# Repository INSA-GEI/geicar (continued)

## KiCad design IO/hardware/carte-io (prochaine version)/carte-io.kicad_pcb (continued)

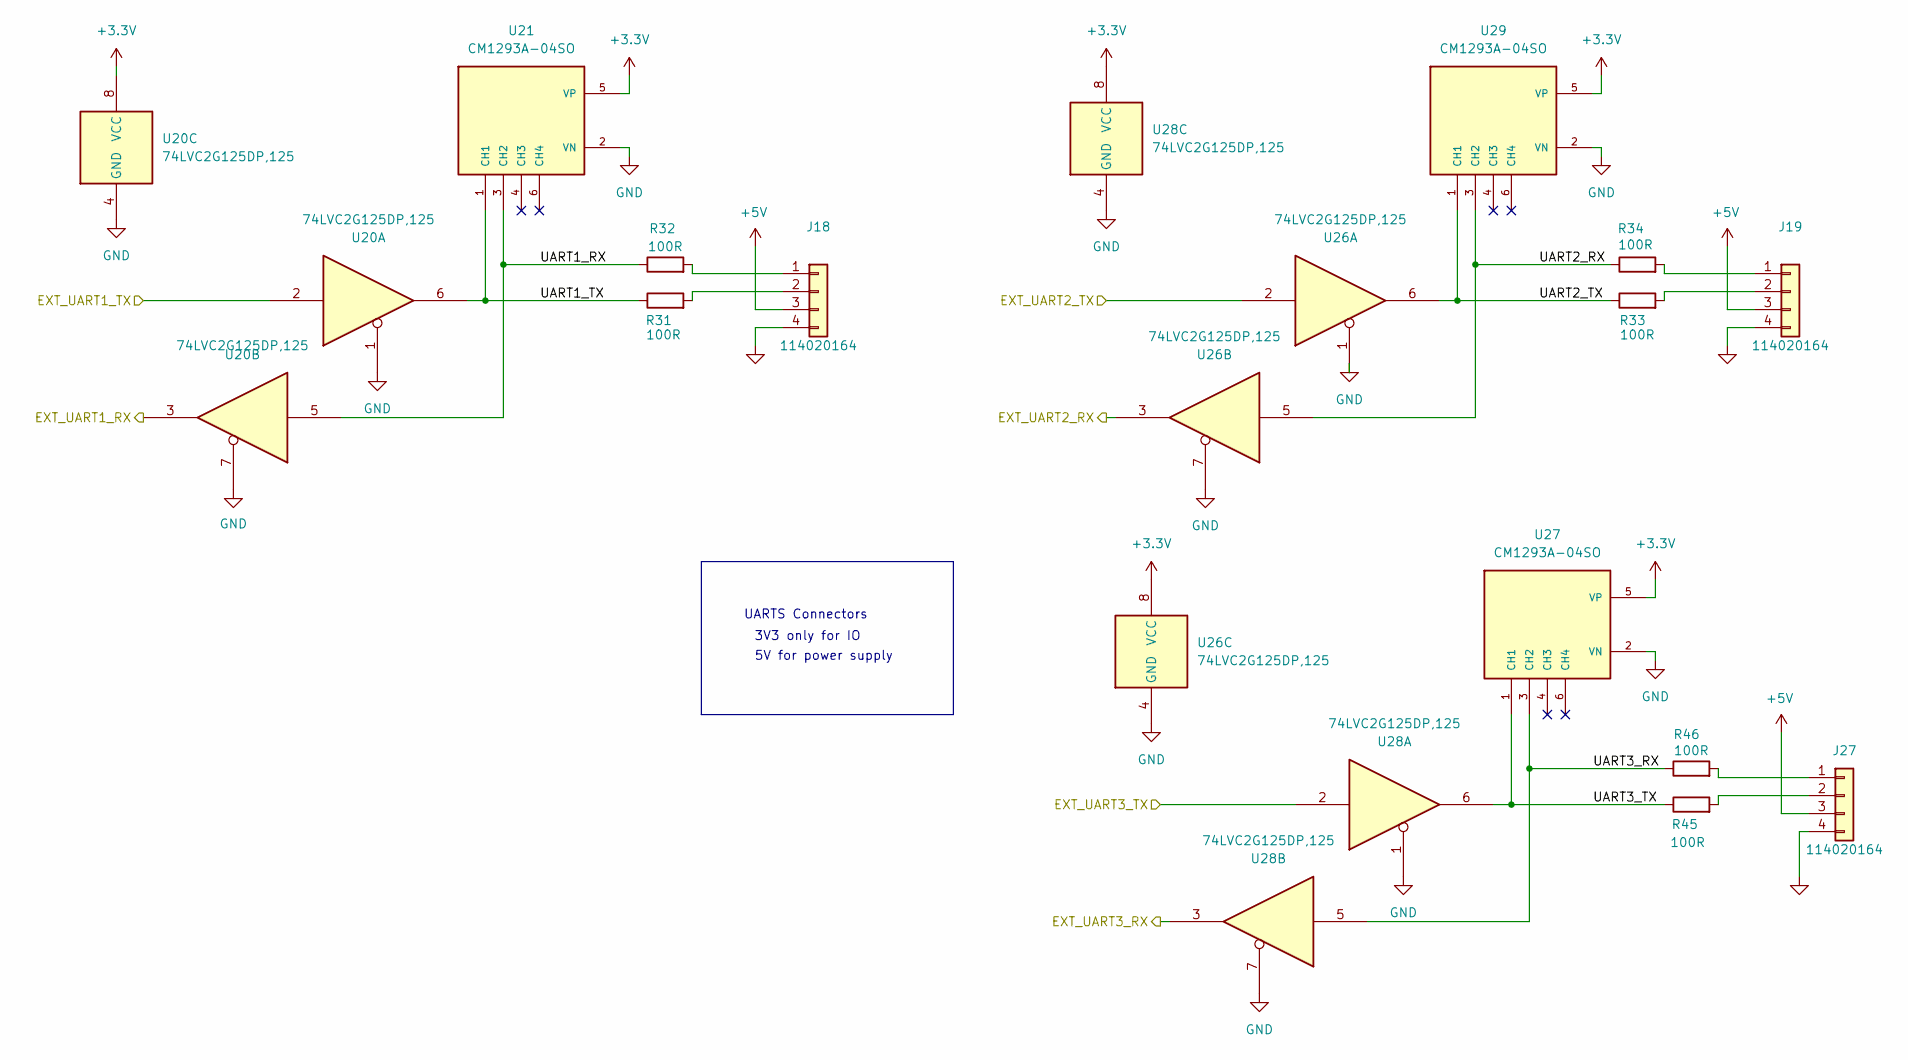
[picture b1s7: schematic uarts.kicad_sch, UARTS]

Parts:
J18, J19, J27: 114020164; SEEEDSTUDIO_114020164
R31, R32, R33, R34, R45, R46: 100R; R_0805_2012Metric_Pad1.20x1.40mm_HandSolder
U20, U26, U28: 74LVC2G125DP,125; TSSOP-8_3x3mm_P0.65mm
U21, U27, U29: CM1293A-04SO; SOT95P285X140-6N

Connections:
+3.3V: U20.8 (VCC), U21.5 (VP), U26.8 (VCC), U27.5 (VP), U28.8 (VCC), U29.5 (VP); also elsewhere on the board
+5V: J18.3, J19.3, J27.3; also elsewhere on the board
/CPU/COM_GPS_RX: U28.2; also elsewhere on the board
/CPU/COM_GPS_TX: U28.3; also elsewhere on the board
/CPU/COM_LIDAR1_RX: U20.3; also elsewhere on the board
/CPU/COM_LIDAR1_TX: U20.2; also elsewhere on the board
/CPU/COM_LIDAR2_RX: U26.3; also elsewhere on the board
/CPU/COM_LIDAR2_TX: U26.2; also elsewhere on the board
/UARTS/UART1_RX: R32.1, U20.5, U21.3 (CH2)
/UARTS/UART1_TX: R31.1, U20.6, U21.1 (CH1)
/UARTS/UART2_RX: R34.1, U26.5, U29.3 (CH2)
/UARTS/UART2_TX: R33.1, U26.6, U29.1 (CH1)
/UARTS/UART3_RX: R46.1, U27.3 (CH2), U28.5
/UARTS/UART3_TX: R45.1, U27.1 (CH1), U28.6
GND: J18.4, J19.4, J27.4, U20.1, U20.4 (GND), U20.7, U21.2 (VN), U26.1, U26.4 (GND), U26.7, U27.2 (VN), U28.1, U28.4 (GND), U28.7, U29.2 (VN); also elsewhere on the board
unnamed: J18.1, R32.2
unnamed: J18.2, R31.2
unnamed: J19.1, R34.2
unnamed: J19.2, R33.2
unnamed: J27.1, R46.2
unnamed: J27.2, R45.2

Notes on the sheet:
UARTS Connectors
5V for power supply
3V3 only for IO

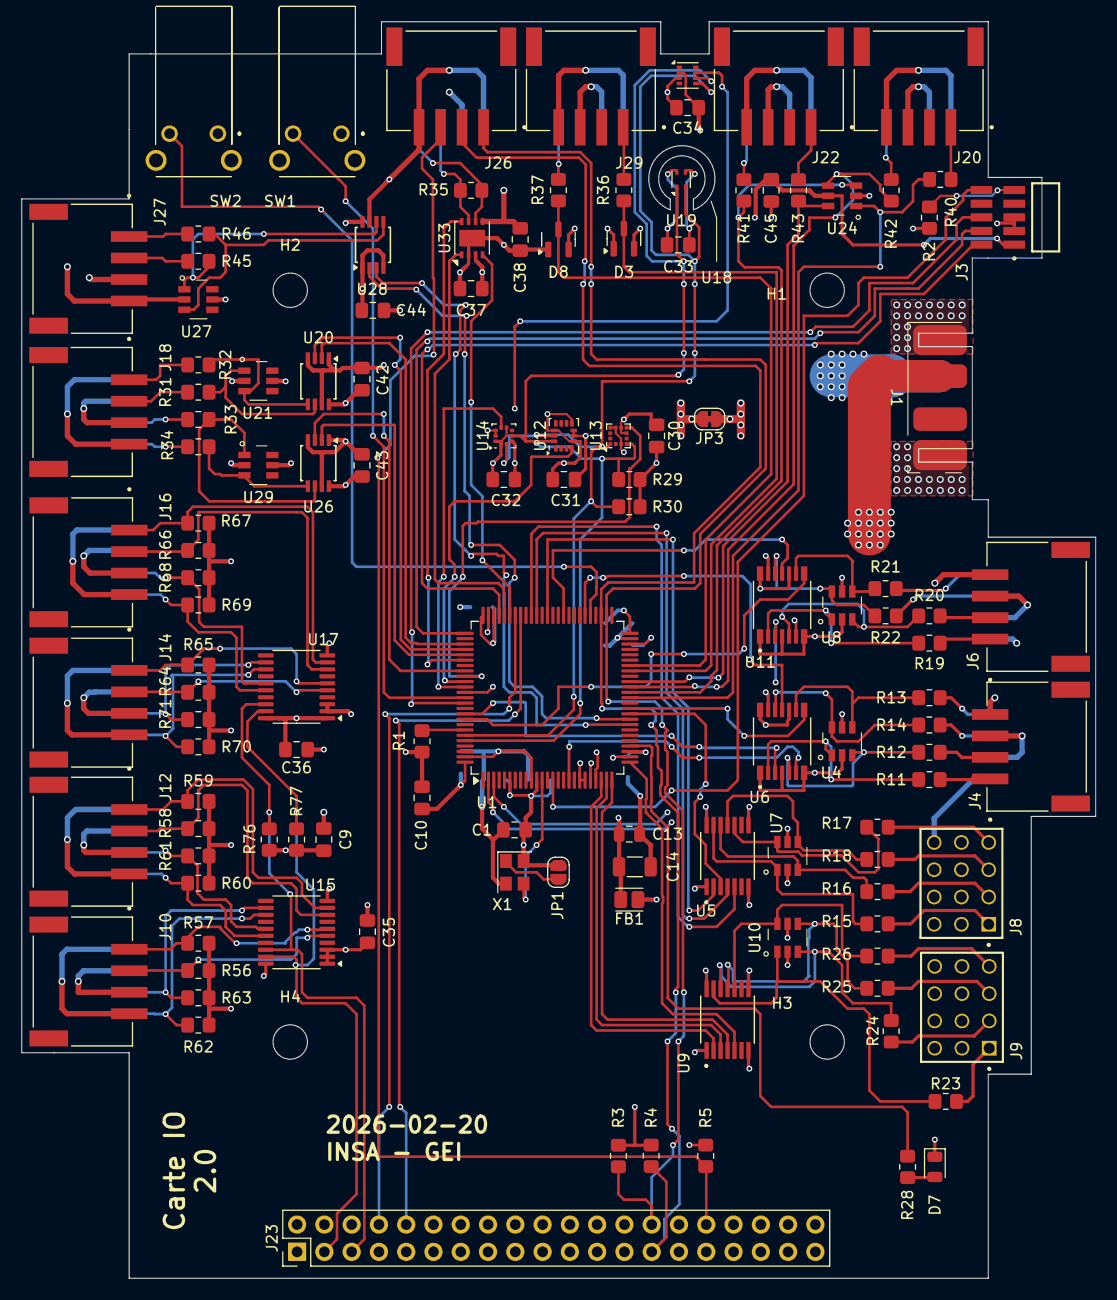
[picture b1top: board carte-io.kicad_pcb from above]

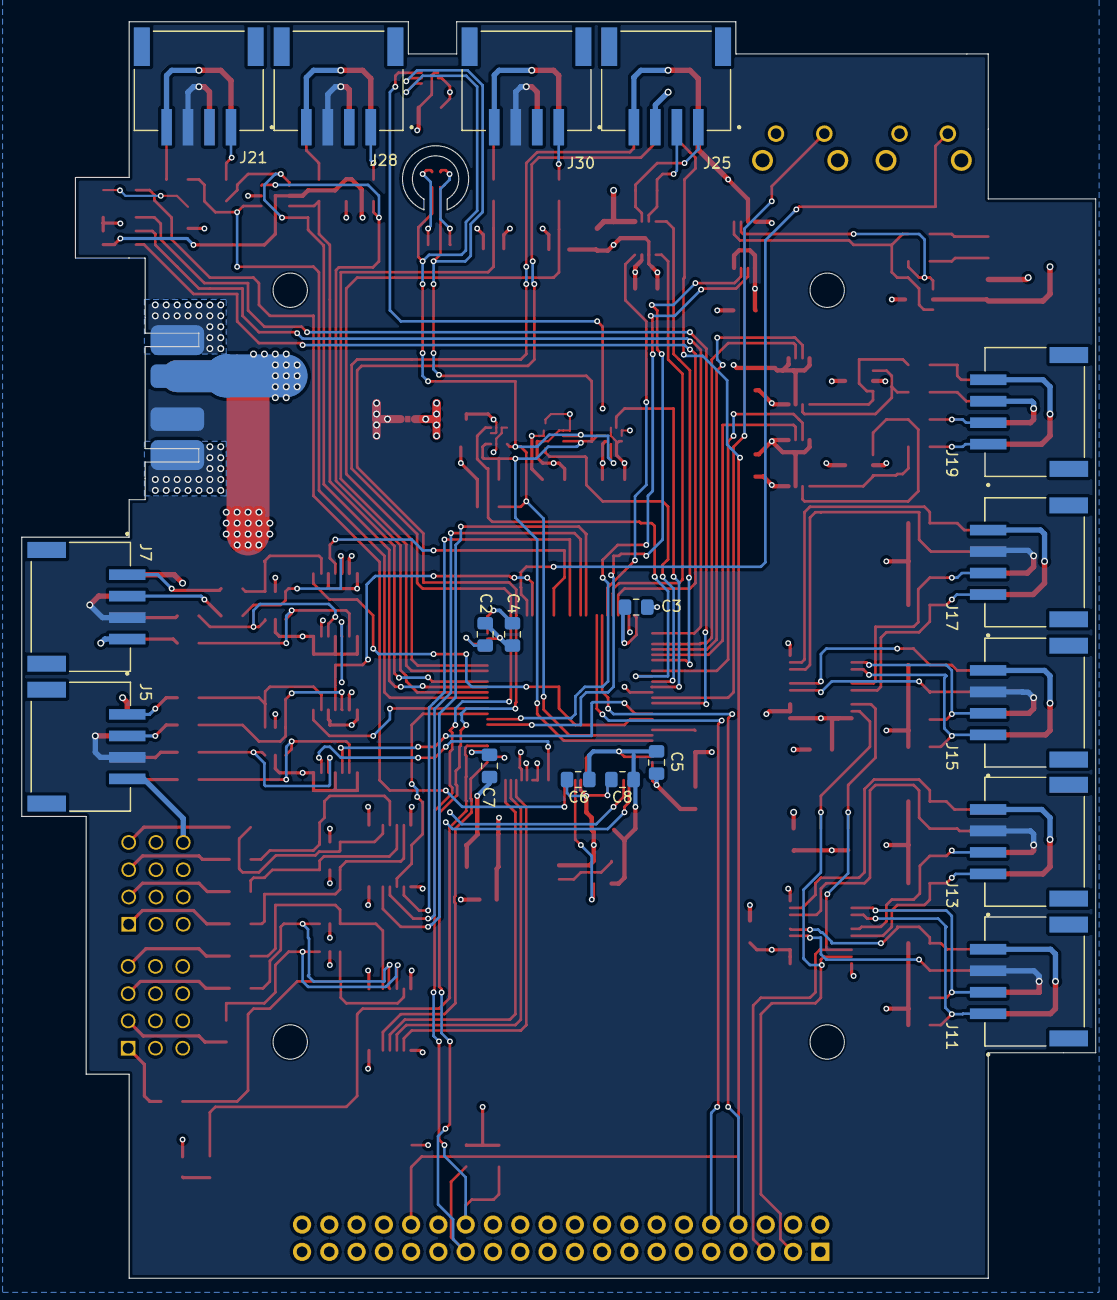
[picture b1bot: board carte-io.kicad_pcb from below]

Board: 4 copper layers, 100.0 x 117.0 mm, 145 parts (18 on the bottom side), 131 nets.

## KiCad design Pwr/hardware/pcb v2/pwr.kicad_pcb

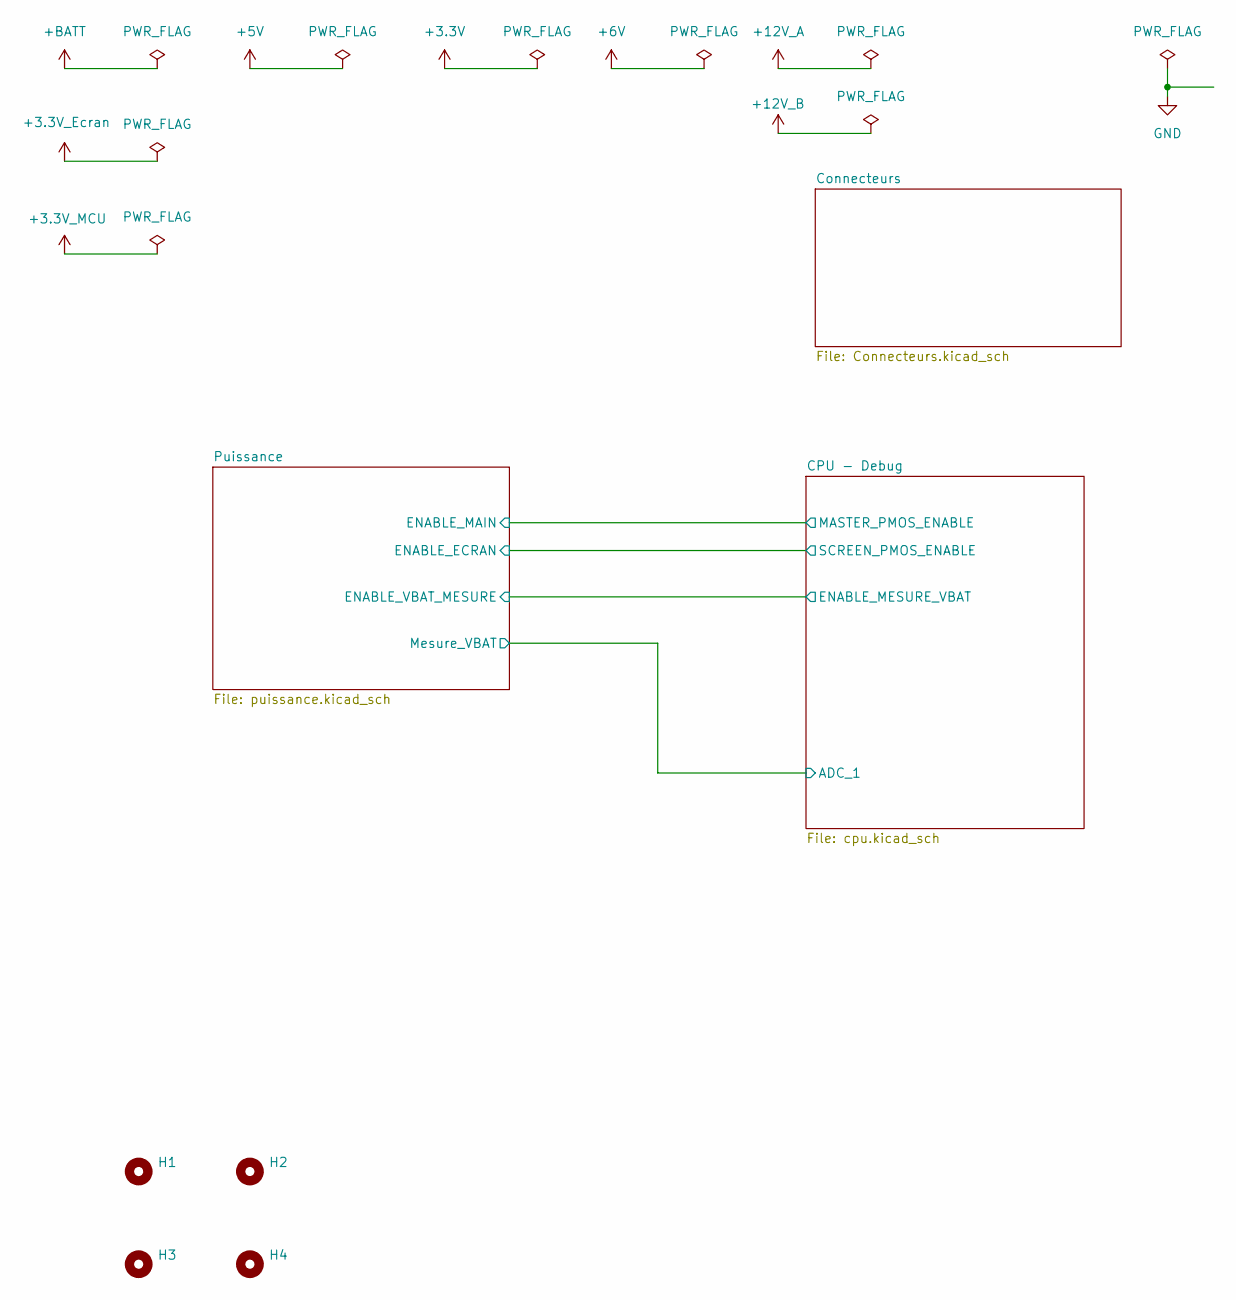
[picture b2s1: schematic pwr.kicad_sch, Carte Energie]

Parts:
H1, H2, H3, H4: MountingHole; MountingHole_3.2mm_M3

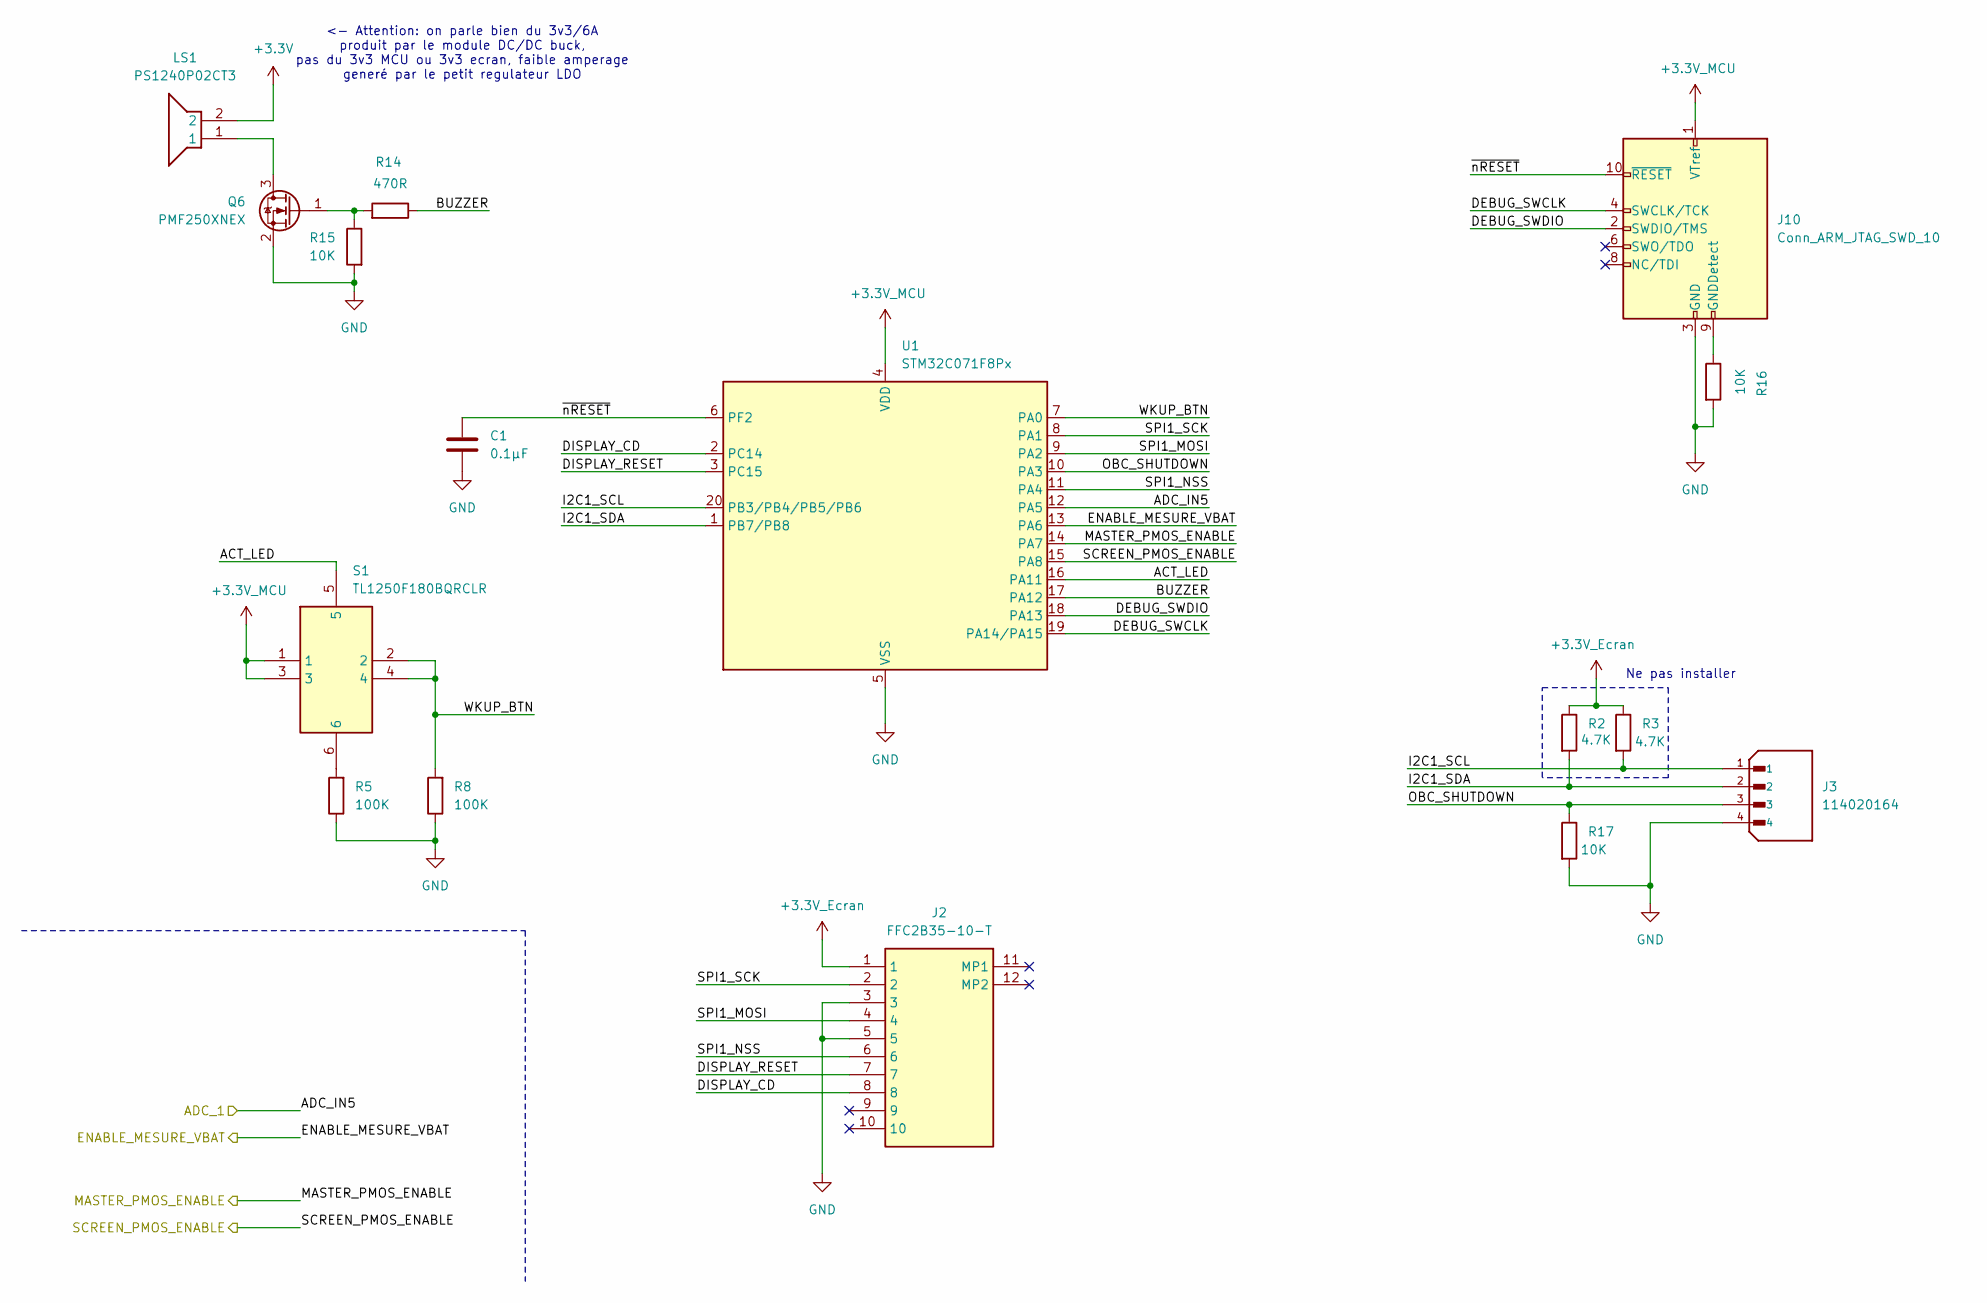
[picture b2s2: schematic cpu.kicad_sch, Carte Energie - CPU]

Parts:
C1: 0.1µF; C_0805_2012Metric
J2: FFC2B35-10-T; FFC2B3510T; Mouser Part Number 640-FFC2B35-10-T
J3: 114020164; SEEEDSTUDIO_114020164; PARTREV 18/5/20
J10: Conn_ARM_JTAG_SWD_10; FTSH10501LDV007K
LS1: PS1240P02CT3; PS1240P02BT; Mouser Part Number 810-PS1240P02CT3
Q6: PMF250XNEX; SOT-323_SC-70
R2, R3: 4.7K; R_0805_2012Metric
R5, R8: 100K; R_0805_2012Metric
R14: 470R; R_0805_2012Metric
R15, R16, R17: 10K; R_0805_2012Metric
S1: TL1250F180BQRCLR; TL1250; Mouser Part Number 612-TL1250F180BQRCLR
U1: STM32C071F8Px; TSSOP-20_4.4x6.5mm_P0.65mm

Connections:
+3.3V: LS1.2; also elsewhere on the board
+3.3V_Ecran: J2.1, R2.1, R3.1; also elsewhere on the board
+3.3V_MCU: J10.1 (VTref), S1.1, S1.3, U1.4 (VDD); also elsewhere on the board
/CPU - Debug/ACT_LED: S1.5, U1.16 (PA11)
/CPU - Debug/ADC_IN5: U1.12 (PA5); also elsewhere on the board
/CPU - Debug/BUZZER: R14.1, U1.17 (PA12)
/CPU - Debug/DEBUG_SWCLK: J10.4 (SWCLK/TCK), U1.19 (PA14/PA15)
/CPU - Debug/DEBUG_SWDIO: J10.2 (SWDIO/TMS), U1.18 (PA13)
/CPU - Debug/DISPLAY_CD: J2.8, U1.2 (PC14)
/CPU - Debug/DISPLAY_RESET: J2.7, U1.3 (PC15)
/CPU - Debug/ENABLE_MESURE_VBAT: U1.13 (PA6); also elsewhere on the board
/CPU - Debug/I2C1_SCL: J3.1, R3.2, U1.20 (PB3/PB4/PB5/PB6)
/CPU - Debug/I2C1_SDA: J3.2, R2.2, U1.1 (PB7/PB8)
/CPU - Debug/MASTER_PMOS_ENABLE: U1.14 (PA7); also elsewhere on the board
/CPU - Debug/OBC_SHUTDOWN: J3.3, R17.1, U1.10 (PA3)
/CPU - Debug/SCREEN_PMOS_ENABLE: U1.15 (PA8); also elsewhere on the board
/CPU - Debug/SPI1_MOSI: J2.4, U1.9 (PA2)
/CPU - Debug/SPI1_NSS: J2.6, U1.11 (PA4)
/CPU - Debug/SPI1_SCK: J2.2, U1.8 (PA1)
/CPU - Debug/WKUP_BTN: R8.2, S1.2, S1.4, U1.7 (PA0)
/CPU - Debug/~nRESET: C1.1, J10.10 (~RESET), U1.6 (PF2)
GND: C1.2, J2.3, J2.5, J3.4, J10.3 (GND), J10.5 (GND), Q6.2 (S), R5.1, R8.1, R15.2, R16.2, R17.2, U1.5 (VSS); also elsewhere on the board
unnamed: J10.9 (GNDDetect), R16.1
unnamed: LS1.1, Q6.3 (D)
unnamed: Q6.1 (G), R14.2, R15.1
unnamed: R5.2, S1.6

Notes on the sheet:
<- Attention: on parle bien du 3v3/6A produit par le module DC/DC buck, pas du 3v3 MCU ou 3v3 ecran, faible amperage generé par le petit regulateur LDO
Ne pas installer

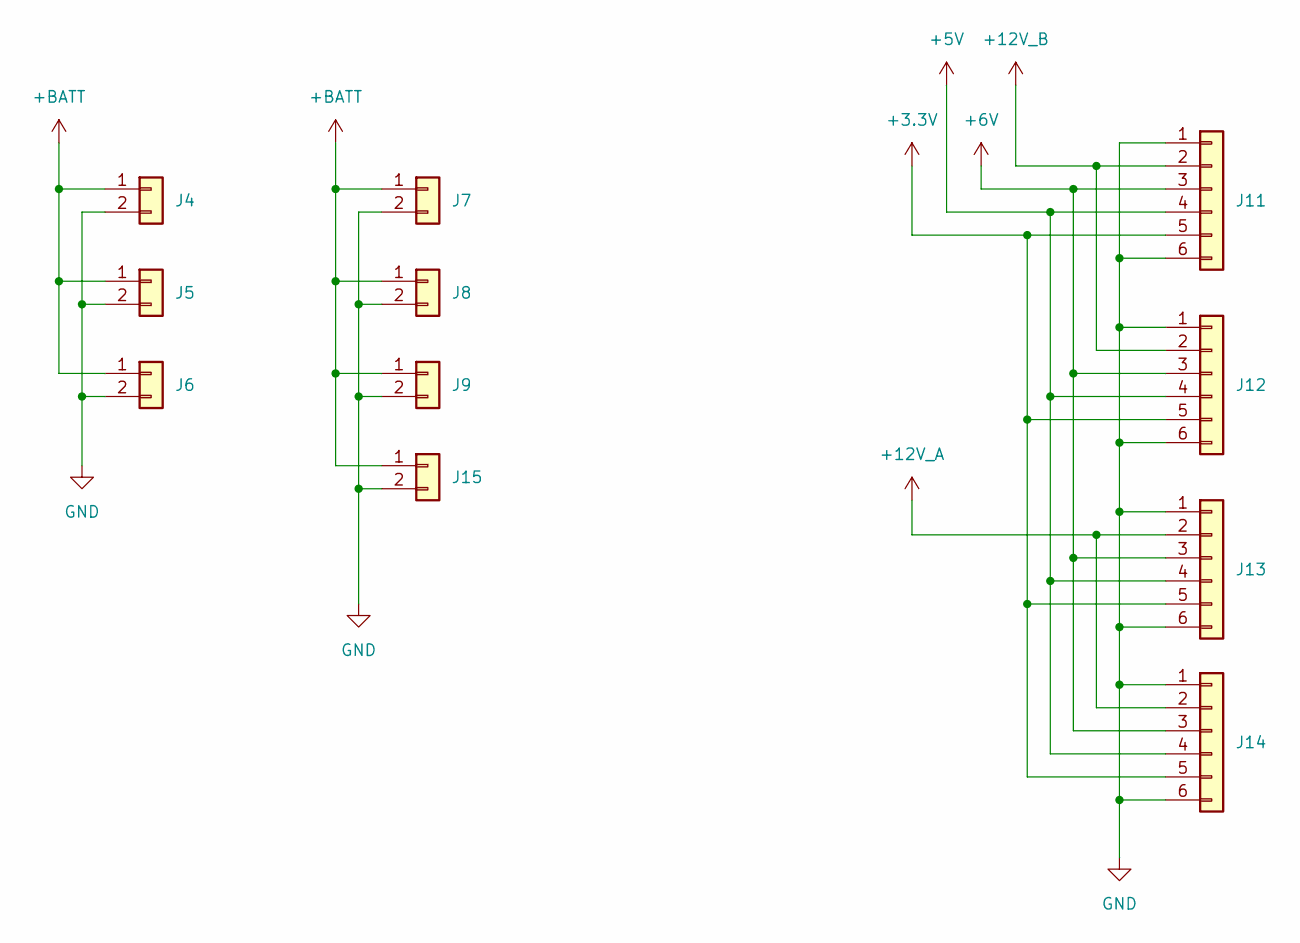
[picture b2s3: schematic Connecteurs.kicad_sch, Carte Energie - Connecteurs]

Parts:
J4, J15: XT60; PAD_XT60
J5, J6, J7, J8, J9: Conn_01x02; PAD_XT60
J11, J12, J13, J14: Conn_01x06; MPX6

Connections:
+3.3V: J11.5, J12.5, J13.5, J14.5; also elsewhere on the board
+5V: J11.4, J12.4, J13.4, J14.4; also elsewhere on the board
+6V: J11.3, J12.3, J13.3, J14.3; also elsewhere on the board
+12V_A: J13.2, J14.2; also elsewhere on the board
+12V_B: J11.2, J12.2; also elsewhere on the board
+BATT: J4.1, J5.1, J6.1, J7.1, J8.1, J9.1, J15.1; also elsewhere on the board
GND: J4.2, J5.2, J6.2, J7.2, J8.2, J9.2, J11.1, J11.6, J12.1, J12.6, J13.1, J13.6, J14.1, J14.6, J15.2; also elsewhere on the board

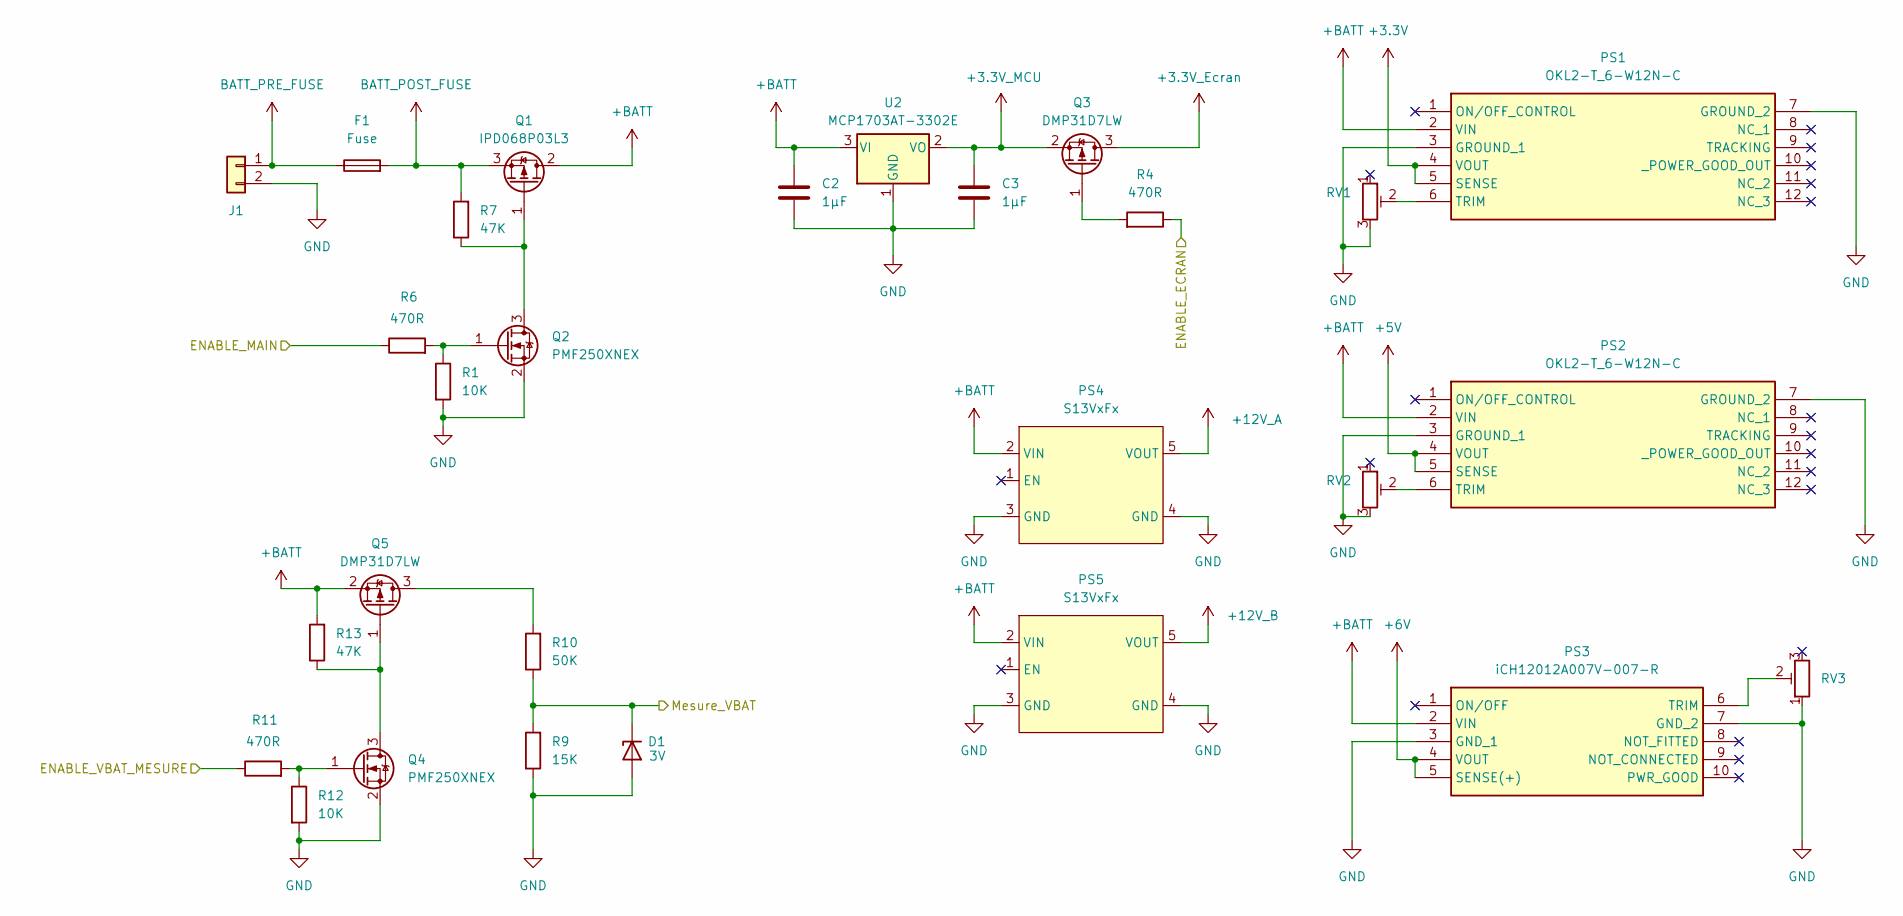
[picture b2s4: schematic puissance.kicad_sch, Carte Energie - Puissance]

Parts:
C2, C3: 1µF; C_0805_2012Metric
D1: 3V; D_SOD-323
F1: Fuse; 3557
J1: XT60; PAD_XT60
PS1, PS2: OKL2-T_6-W12N-C; OKL2T6W12NC; Mouser Part Number 580-OKL2-T/6-W12N-C
PS3: iCH12012A007V-007-R; ICH12012A007V007R; Mouser Part Number 967-ICH12012A007V007
PS4, PS5: S13VxFx
Q1: IPD068P03L3; TO-252-2
Q2, Q4: PMF250XNEX; SOT-323_SC-70
Q3, Q5: DMP31D7LW; SOT-323_SC-70
R1, R12: 10K; R_0805_2012Metric
R4, R6, R11: 470R; R_0805_2012Metric
R7, R13: 47K; R_0805_2012Metric
R9: 15K; R_0805_2012Metric
R10: 50K; R_0805_2012Metric
RV1, RV2, RV3: 3214W-1-202E; Potentiometer_Bourns_3214W_Vertical
U2: MCP1703AT-3302E; SOT-23

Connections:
+3.3V: PS1.4 (VOUT), PS1.5 (SENSE); also elsewhere on the board
+3.3V_Ecran: Q3.3 (D); also elsewhere on the board
+3.3V_MCU: C3.1, Q3.2 (S), U2.2 (VO); also elsewhere on the board
+5V: PS2.4 (VOUT), PS2.5 (SENSE); also elsewhere on the board
+6V: PS3.4 (VOUT), PS3.5 (SENSE(+)); also elsewhere on the board
+12V_A: PS4.5 (VOUT); also elsewhere on the board
+12V_B: PS5.5 (VOUT); also elsewhere on the board
+BATT: C2.1, PS1.2 (VIN), PS2.2 (VIN), PS3.2 (VIN), PS4.2 (VIN), PS5.2 (VIN), Q1.2 (D), Q5.2 (S), R13.2, U2.3 (VI); also elsewhere on the board
/CPU - Debug/ADC_IN5: D1.1 (K), R9.2, R10.1; also elsewhere on the board
/CPU - Debug/ENABLE_MESURE_VBAT: R11.1; also elsewhere on the board
/CPU - Debug/MASTER_PMOS_ENABLE: R6.1; also elsewhere on the board
/CPU - Debug/SCREEN_PMOS_ENABLE: R4.1; also elsewhere on the board
BATT_POST_FUSE: F1.2, Q1.3 (S), R7.2
BATT_PRE_FUSE: F1.1, J1.1
GND: C2.2, C3.2, D1.2 (A), J1.2, PS1.3 (GROUND_1), PS1.7 (GROUND_2), PS2.3 (GROUND_1), PS2.7 (GROUND_2), PS3.3 (GND_1), PS3.7 (GND_2), PS4.3 (GND), PS4.4 (GND), PS5.3 (GND), PS5.4 (GND), Q2.2 (S), Q4.2 (S), R1.2, R9.1, R12.2, RV1.3, RV2.3, RV3.1, U2.1 (GND); also elsewhere on the board
unnamed: PS1.6 (TRIM), RV1.2
unnamed: PS2.6 (TRIM), RV2.2
unnamed: PS3.6 (TRIM), RV3.2
unnamed: Q1.1 (G), Q2.3 (D), R7.1
unnamed: Q2.1 (G), R1.1, R6.2
unnamed: Q3.1 (G), R4.2
unnamed: Q4.3 (D), Q5.1 (G), R13.1
unnamed: Q4.1 (G), R11.2, R12.1
unnamed: Q5.3 (D), R10.2

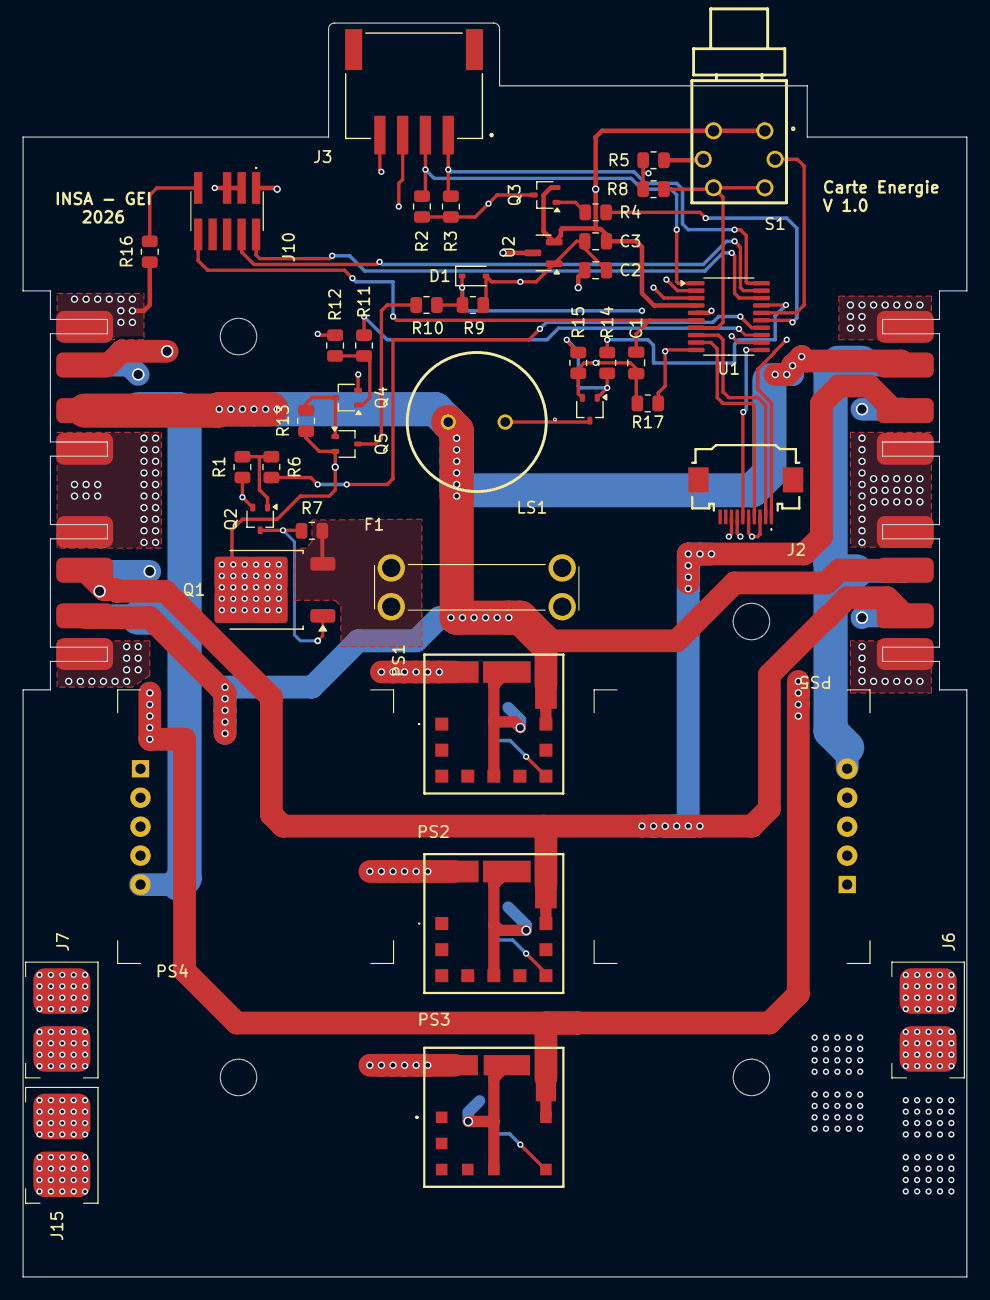
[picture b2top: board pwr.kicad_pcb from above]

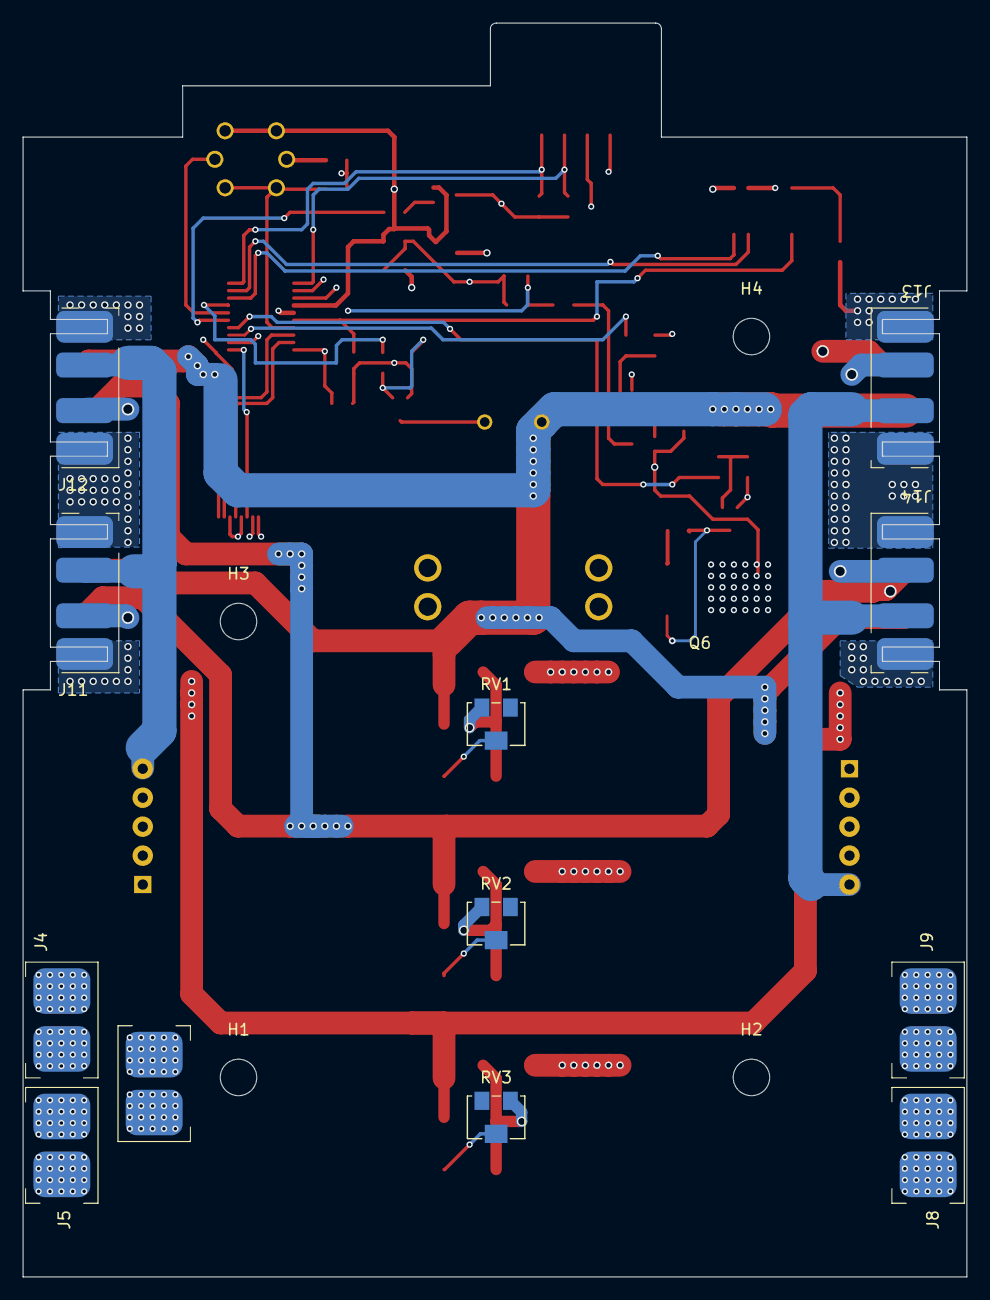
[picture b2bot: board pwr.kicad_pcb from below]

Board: 4 copper layers, 82.8 x 110.0 mm, 59 parts (16 on the bottom side), 42 nets.

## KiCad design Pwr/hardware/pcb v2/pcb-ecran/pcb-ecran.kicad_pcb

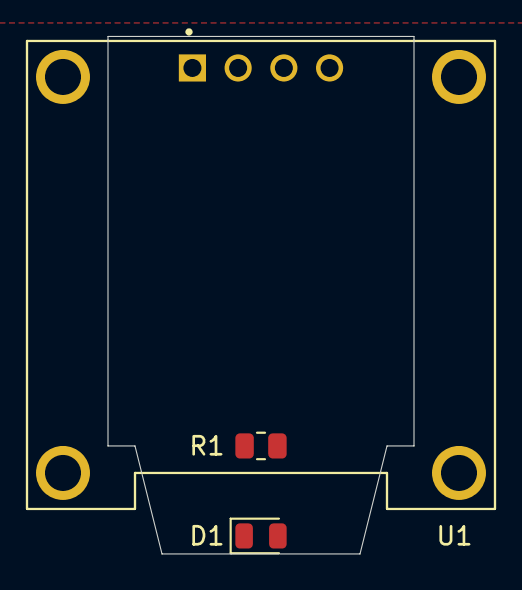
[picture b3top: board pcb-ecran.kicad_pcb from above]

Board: 2 copper layers, 17.0 x 28.8 mm, 4 parts (1 on the bottom side), 6 nets, no tracks yet.

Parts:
D1: APT2012LSECK/J3-PRV; LED_0805_2012Metric
J1: FFC2B35-10-T; FFC2B3510T
R1: 1K; R_0805_2012Metric
U1: DM-OLED096-636; MODULE_DM-OLED096-636

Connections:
+3.3V_Ecran: J1.1, U1.2 (VCC_IN)
/RED_LED: D1.2 (A), J1.7
/SPI_DATA: J1.4, U1.4 (SDA)
/SPI_SCK: J1.2, U1.3 (SCL)
GND: J1.3, J1.5, R1.2, U1.1 (GND)
unnamed: D1.1 (K), R1.1

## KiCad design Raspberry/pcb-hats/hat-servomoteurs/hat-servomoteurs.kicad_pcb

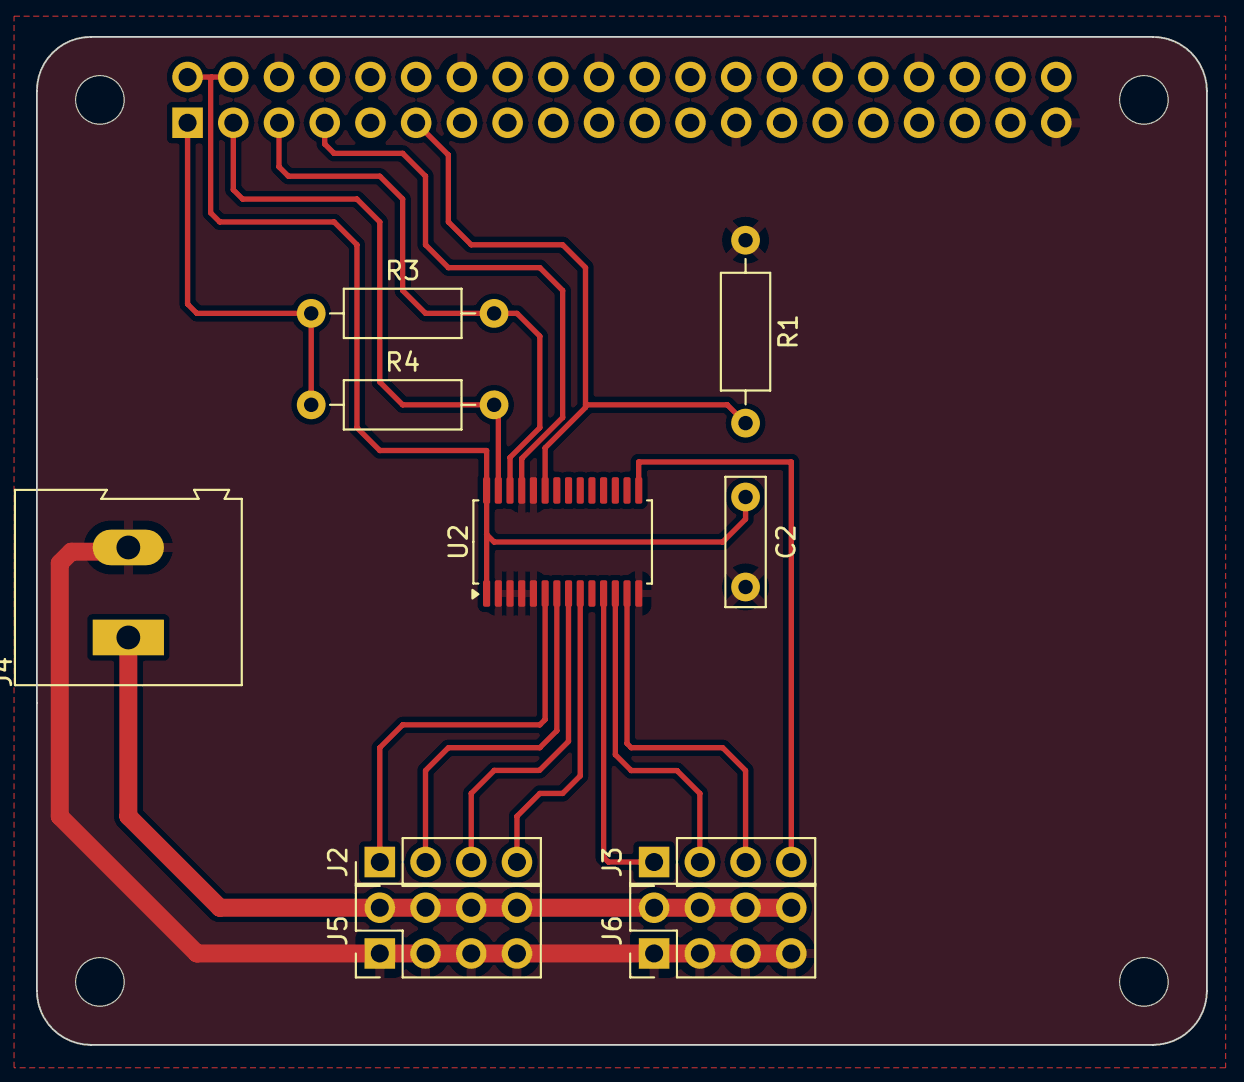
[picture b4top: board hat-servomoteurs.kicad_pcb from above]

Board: 2 copper layers, 65.0 x 56.0 mm, 15 parts (1 on the bottom side), 15 nets.

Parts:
C2: 100nf; C_Rect_L7.0mm_W2.0mm_P5.00mm
J1: GPIO; PinSocket_2x20_P2.54mm_Vertical
J2: Servomoteurs; PinHeader_1x04_P2.54mm_Vertical
J3: ESC; PinHeader_1x04_P2.54mm_Vertical
J4: Conn_01x02; TerminalBlock_Altech_AK300-2_P5.00mm
J5, J6: Conn_02x04_Odd_Even; PinHeader_2x04_P2.54mm_Vertical
MH1, MH2, MH3, MH4: MountingHole_2.7mm_M2.5
R1: 1M; R_Axial_DIN0207_L6.3mm_D2.5mm_P10.16mm_Horizontal
R3, R4: 4.7K; R_Axial_DIN0207_L6.3mm_D2.5mm_P10.16mm_Horizontal
U2: PCA9685PW; TSSOP-28_4.4x9.7mm_P0.65mm

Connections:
+3V3: J1.1, J1.17, R3.1, R4.1
+5V: C2.1, J1.2, J1.4, U2.1 (A0), U2.28 (VDD)
+BATT: J4.1, J5.2, J5.4, J5.6, J5.8, J6.2, J6.4, J6.6, J6.8
/GPIO2/SDA1: J1.3, R4.2, U2.27 (SDA)
/GPIO3/SCL1: J1.5, R3.2, U2.26 (SCL)
/GPIO17: J1.11, R1.2, U2.23 (~OE)
GND: C2.2, J1.6, J1.9, J1.14, J1.20, J1.25, J1.30, J1.34, J1.39, J4.2, J5.1, J5.3, J5.5, J5.7, J6.1, J6.3, J6.5, J6.7, R1.1, U2.2 (A1), U2.3 (A2), U2.4 (A3), U2.5 (A4), U2.14 (VSS), U2.24 (A5), U2.25 (EXTCLK)
unnamed: J2.1, U2.6 (LED0)
unnamed: J2.2, U2.7 (LED1)
unnamed: J2.3, U2.8 (LED2)
unnamed: J2.4, U2.9 (LED3)
unnamed: J3.1, U2.11 (LED5)
unnamed: J3.2, U2.12 (LED6)
unnamed: J3.3, U2.13 (LED7)
unnamed: J3.4, U2.15 (LED8)
